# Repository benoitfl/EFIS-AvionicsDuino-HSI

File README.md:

# EFIS-AvionicsDuino
This is the software of the EFIS main module described here https://avionicsduino.com/index.php/en/efis-2/

This module is based on a PJRC Teensy 4.1 board.

# HSI Branch
This branch is made to add a HSI to this repo.

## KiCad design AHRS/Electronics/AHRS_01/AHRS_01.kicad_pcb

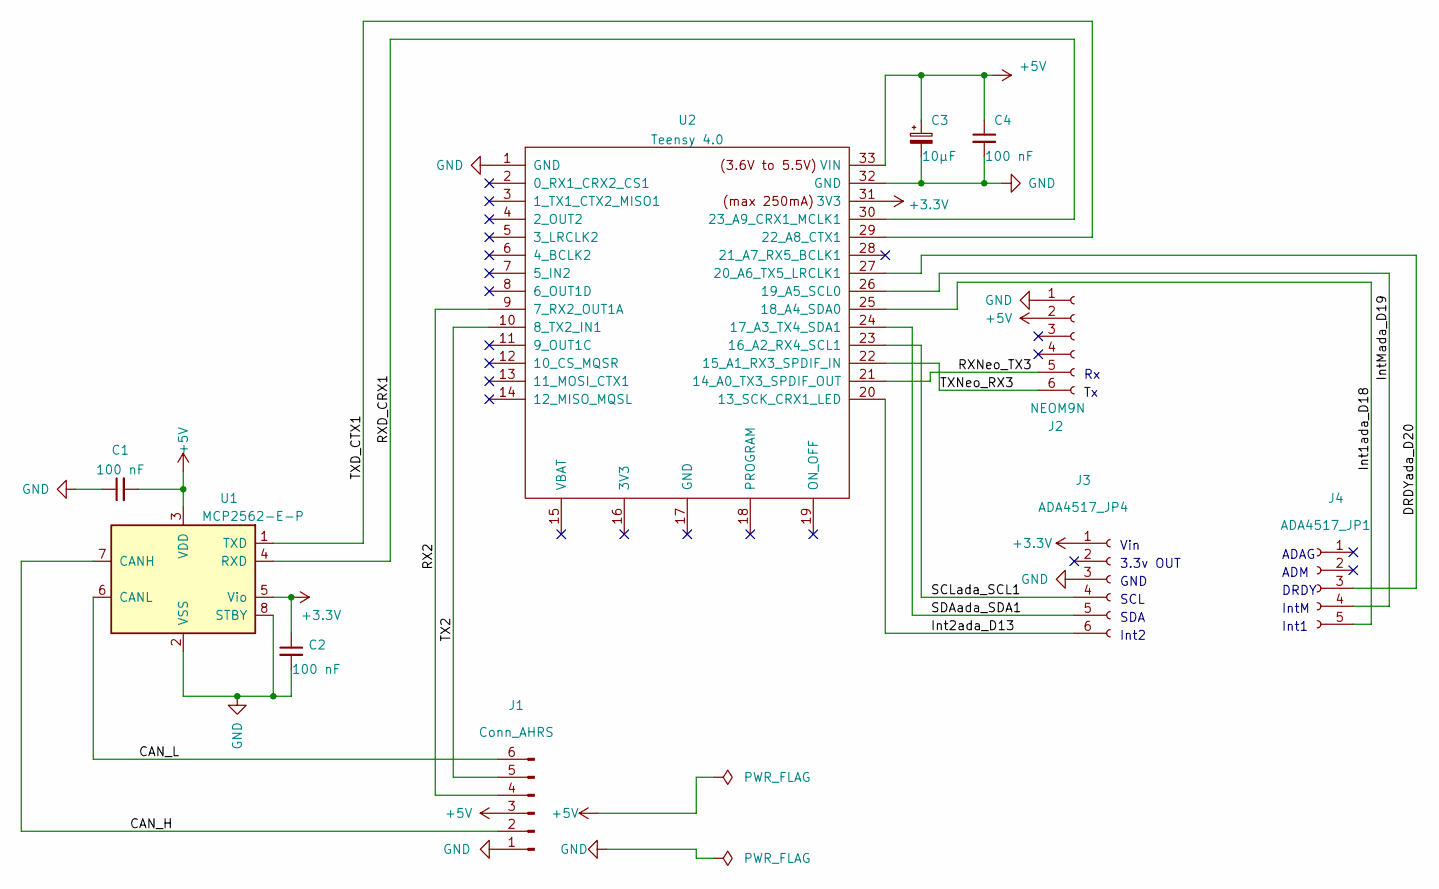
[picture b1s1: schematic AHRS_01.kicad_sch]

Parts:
C1, C2, C4: 100 nF; C_1206_3216Metric_Pad1.33x1.80mm_HandSolder
C3: 10µF; CP_EIA-7343-31_Kemet-D_Pad2.25x2.55mm_HandSolder
J1: Conn_AHRS; JST_EH_S6B-EH_1x06_P2.50mm_Horizontal
J2: NEOM9N; PinSocket_1x06_P2.54mm_Vertical
J3: ADA4517_JP4; PinSocket_1x06_P2.54mm_Vertical
J4: ADA4517_JP1; PinSocket_1x05_P2.54mm_Vertical
U1: MCP2562-E-P; DIP-8_W7.62mm
U2: Teensy 4.0; Teensy4FrontSide

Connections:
+3V3: C2.1, J3.1, U1.5 (Vio), U2.31 (3V3)
+5V: C1.2, C3.1, C4.1, J1.3, J2.2, U1.3 (VDD), U2.33 (VIN)
/CAN_H: J1.2, U1.7 (CANH)
/CAN_L: J1.6, U1.6 (CANL)
/DRDYada_D20: J4.3, U2.27 (20_A6_TX5_LRCLK1)
/Int1ada_D18: J4.5, U2.25 (18_A4_SDA0)
/Int2ada_D13: J3.6, U2.20 (13_SCK_CRX1_LED)
/IntMada_D19: J4.4, U2.26 (19_A5_SCL0)
/RX2: J1.4, U2.9 (7_RX2_OUT1A)
/RXD_CRX1: U1.4 (RXD), U2.30 (23_A9_CRX1_MCLK1)
/RXNeo_TX3: J2.5, U2.21 (14_A0_TX3_SPDIF_OUT)
/SCLada_SCL1: J3.4, U2.23 (16_A2_RX4_SCL1)
/SDAada_SDA1: J3.5, U2.24 (17_A3_TX4_SDA1)
/TX2: J1.5, U2.10 (8_TX2_IN1)
/TXD_CTX1: U1.1 (TXD), U2.29 (22_A8_CTX1)
/TXNeo_RX3: J2.6, U2.22 (15_A1_RX3_SPDIF_IN)
GND: C1.1, C2.2, C3.2, C4.2, J1.1, J2.1, J3.3, U1.2 (VSS), U1.8 (STBY), U2.1 (GND), U2.32 (GND)

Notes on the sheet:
DRDY
3.3v OUT
Vin
SCL
ADAG
Int1
SDA
Int2
IntM
ADM
GND

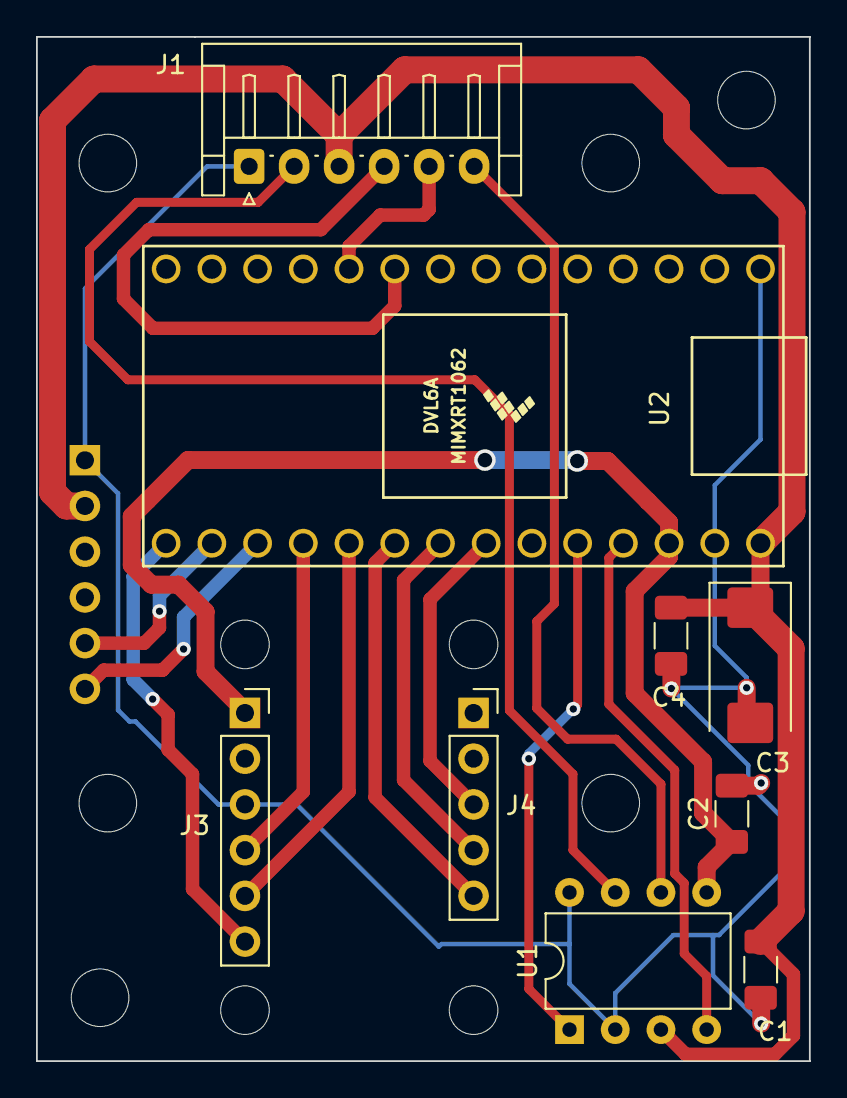
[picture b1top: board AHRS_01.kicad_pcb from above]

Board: 2 copper layers, 42.9 x 56.9 mm, 10 parts (1 on the bottom side), 17 nets.

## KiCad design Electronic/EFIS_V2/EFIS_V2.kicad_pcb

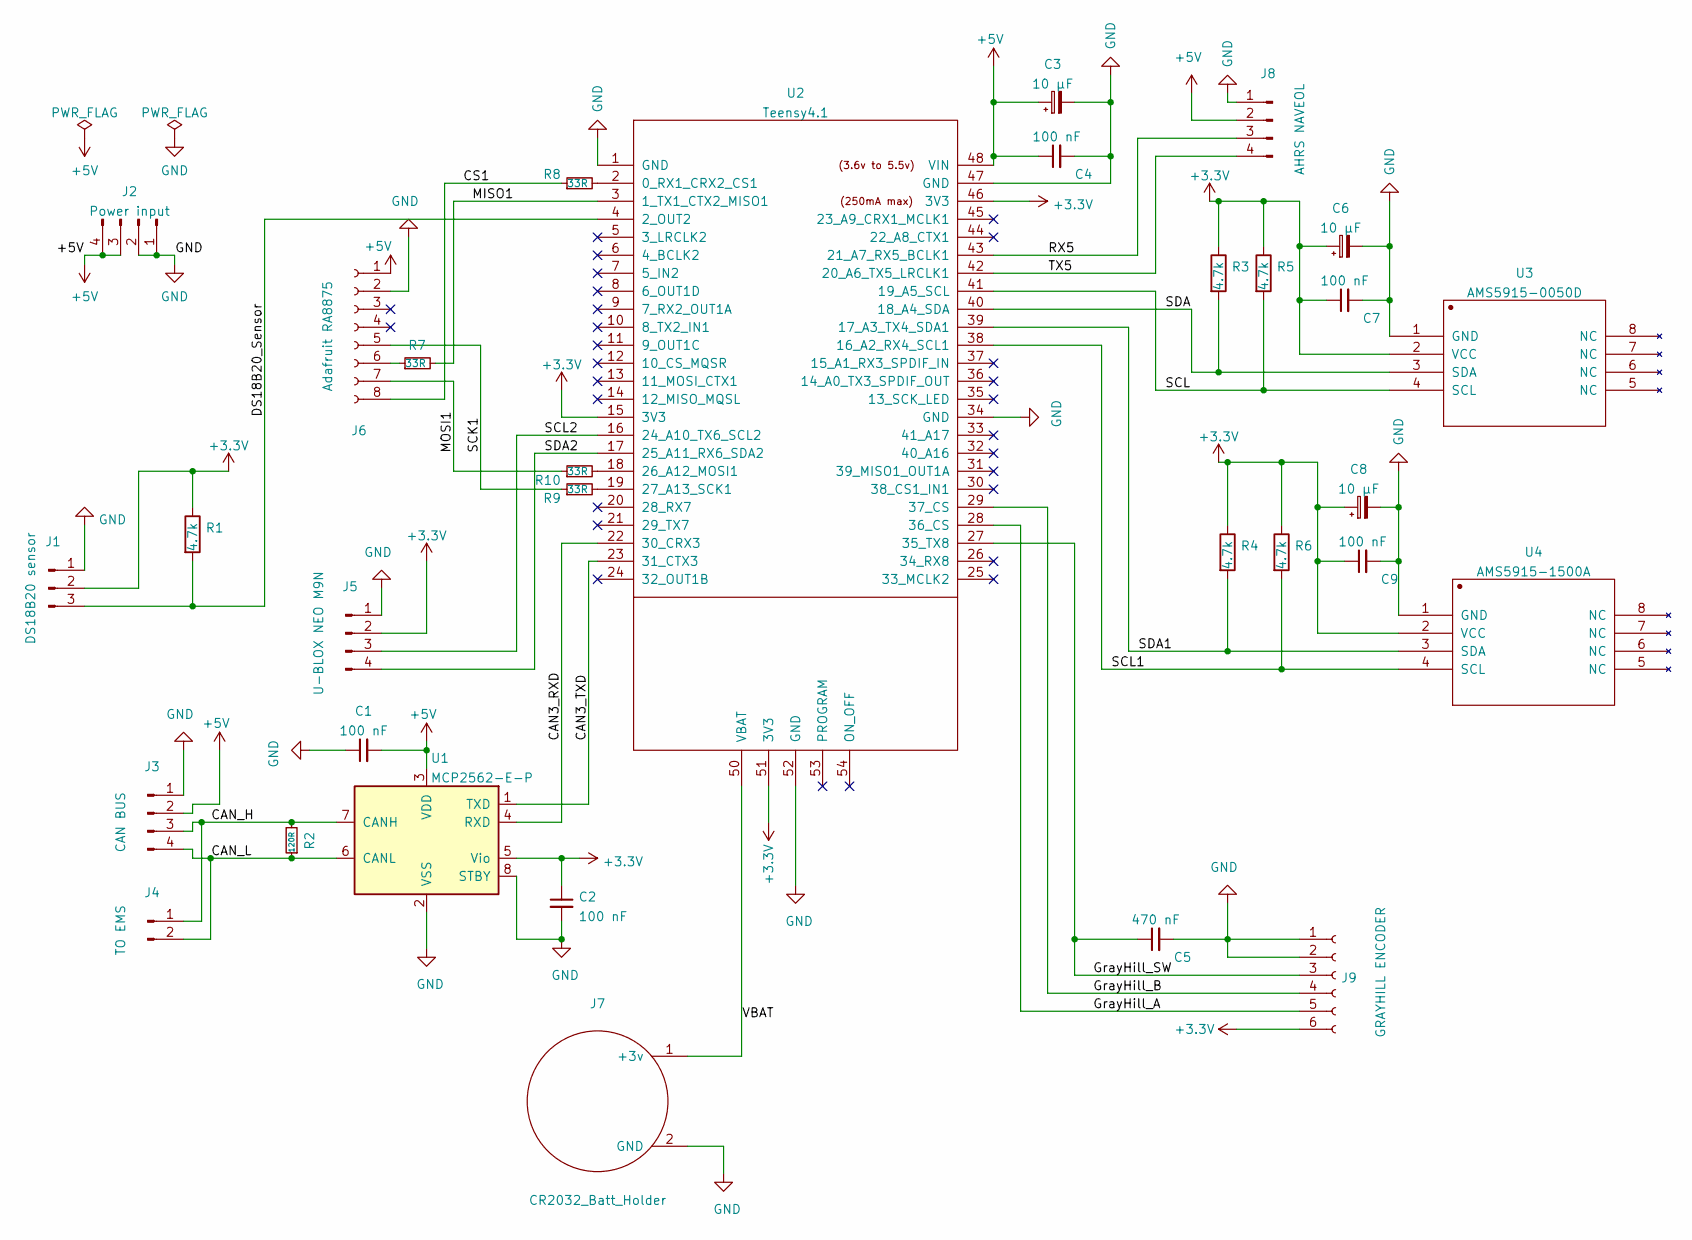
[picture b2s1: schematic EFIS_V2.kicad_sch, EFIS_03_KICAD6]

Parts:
C1, C2, C4, C7, C9: 100 nF; C_1206_3216Metric_Pad1.33x1.80mm_HandSolder
C3, C6, C8: 10 µF; CP_EIA-7343-31_Kemet-D_Pad2.25x2.55mm_HandSolder
C5: 470 nF; C_1206_3216Metric_Pad1.33x1.80mm_HandSolder
J1: DS18B20 sensor; Molex_KK-254_AE-6410-03A_1x03_P2.54mm_Vertical
J2: Power input; Molex_KK-254_AE-6410-04A_1x04_P2.54mm_Vertical
J3: CAN BUS; Molex_KK-254_AE-6410-04A_1x04_P2.54mm_Vertical
J4: TO EMS; Molex_KK-254_AE-6410-02A_1x02_P2.54mm_Vertical
J5: U-BLOX NEO M9N; Molex_KK-254_AE-6410-04A_1x04_P2.54mm_Vertical
J6: Adafruit RA8875; PinSocket_1x08_P2.54mm_Vertical
J7: CR2032_Batt_Holder; BatteryHolder_Keystone_103_1x20mm
J8: AHRS NAVEOL; Molex_KK-254_AE-6410-04A_1x04_P2.54mm_Vertical
J9: GRAYHILL ENCODER; 3380686
R1, R3, R4, R5, R6: 4.7k; R_1206_3216Metric_Pad1.30x1.75mm_HandSolder
R2: 120R; R_1210_3225Metric_Pad1.30x2.65mm_HandSolder
R7, R8, R9, R10: 33R; R_1206_3216Metric_Pad1.30x1.75mm_HandSolder
U1: MCP2562-E-P; DIP-8_W7.62mm
U2: Teensy4.1; Teensy41
U3: AMS5915-0050D; doublePinSocket_2x04_P2.54mm_Vertical_W15.24mm
U4: AMS5915-1500A; doublePinSocket_2x04_P2.54mm_Vertical_W15.24mm

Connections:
+3V3: C2.1, C6.1, C7.1, C8.1, C9.1, J1.2, J5.2, J9.6, R1.1, R3.1, R4.1, R5.1, R6.1, U1.5 (Vio), U2.15 (3V3), U2.46 (3V3), U2.51 (3V3), U3.2 (VCC), U4.2 (VCC)
+5V: C1.2, C3.1, C4.1, J2.3, J2.4, J3.2, J6.1, J8.2, U1.3 (VDD), U2.48 (VIN)
/CAN3_RXD: U1.4 (RXD), U2.22 (30_CRX3)
/CAN3_TXD: U1.1 (TXD), U2.23 (31_CTX3)
/CAN_H: J3.3, J4.1, R2.2, U1.7 (CANH)
/CAN_L: J3.4, J4.2, R2.1, U1.6 (CANL)
/CS1: J6.8, R8.1
/DS18B20_Sensor: J1.3, R1.2, U2.4 (2_OUT2)
/GrayHill_A: J9.5, U2.28 (36_CS)
/GrayHill_B: J9.4, U2.29 (37_CS)
/GrayHill_SW: C5.1, J9.3, U2.27 (35_TX8)
/MISO1: R7.2, U2.3 (1_TX1_CTX2_MISO1)
/MOSI1: J6.7, R10.1
/RX5: J8.3, U2.43 (21_A7_RX5_BCLK1)
/SCK1: J6.5, R9.1
/SCL: R5.2, U2.41 (19_A5_SCL), U3.4 (SCL)
/SCL1: R6.2, U2.38 (16_A2_RX4_SCL1), U4.4 (SCL)
/SCL2: J5.3, U2.16 (24_A10_TX6_SCL2)
/SDA: R3.2, U2.40 (18_A4_SDA), U3.3 (SDA)
/SDA1: R4.2, U2.39 (17_A3_TX4_SDA1), U4.3 (SDA)
/SDA2: J5.4, U2.17 (25_A11_RX6_SDA2)
/TX5: J8.4, U2.42 (20_A6_TX5_LRCLK1)
/VBAT: J7.1 (+3v), U2.50 (VBAT)
GND: C1.1, C2.2, C3.2, C4.2, C5.2, C6.2, C7.2, C8.2, C9.2, J1.1, J2.1, J2.2, J3.1, J5.1, J6.2, J7.2 (GND), J8.1, J9.1, J9.2, U1.2 (VSS), U1.8 (STBY), U2.1 (GND), U2.34 (GND), U2.47 (GND), U2.52 (GND), U3.1 (GND), U4.1 (GND)
unnamed: J6.6, R7.1
unnamed: R8.2, U2.2 (0_RX1_CRX2_CS1)
unnamed: R9.2, U2.19 (27_A13_SCK1)
unnamed: R10.2, U2.18 (26_A12_MOSI1)

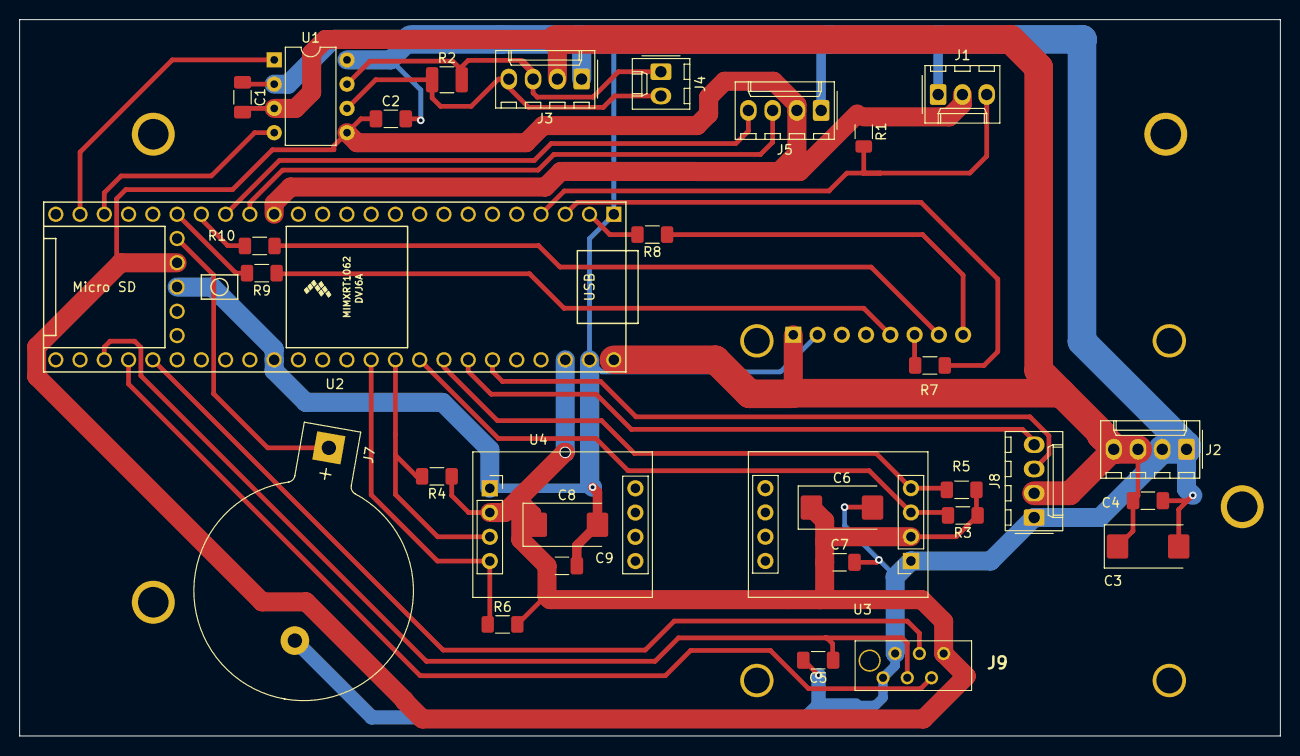
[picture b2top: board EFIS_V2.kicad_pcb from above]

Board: 2 copper layers, 132.0 x 75.0 mm, 32 parts (1 on the bottom side), 28 nets.

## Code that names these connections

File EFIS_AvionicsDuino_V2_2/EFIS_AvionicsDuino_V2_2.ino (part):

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//                   GND           --------->      GND 
//                   VIN           --------->   + 5 Volts
//                    CS           --------->   Pin 0 CS1
//                   MISO          --------->   Pin 1 MISO1
//                   MOSI          --------->   Pin 26 MOSI1
//                   SCK           --------->   Pin 27 SCK1
//             Tout le reste       --------->   Non connecté
//---------------------------------------------------------------------------
// Encodeur rotatif optique GrayHill :
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
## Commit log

2023-02-24 Folder org.
    Adding electronics files to the repo, and reordering stuff.
2023-04-03 HSI Added
    Added HSI option in the menu + a HSI page

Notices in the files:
EFIS_AvionicsDuino_V2_2/EFIS_AvionicsDuino_V2_2.ino:
MIT License (MIT)
Copyright (c) 2023 AvionicsDuino - benjamin.fremond@avionicsduino.com
